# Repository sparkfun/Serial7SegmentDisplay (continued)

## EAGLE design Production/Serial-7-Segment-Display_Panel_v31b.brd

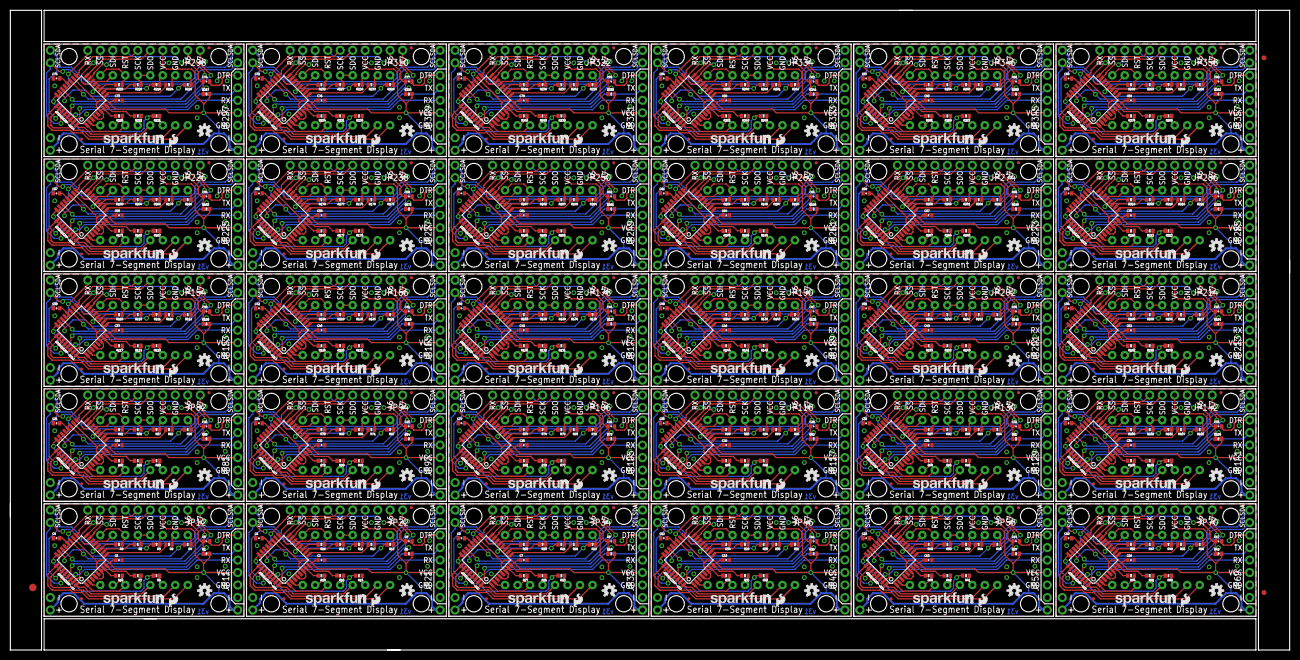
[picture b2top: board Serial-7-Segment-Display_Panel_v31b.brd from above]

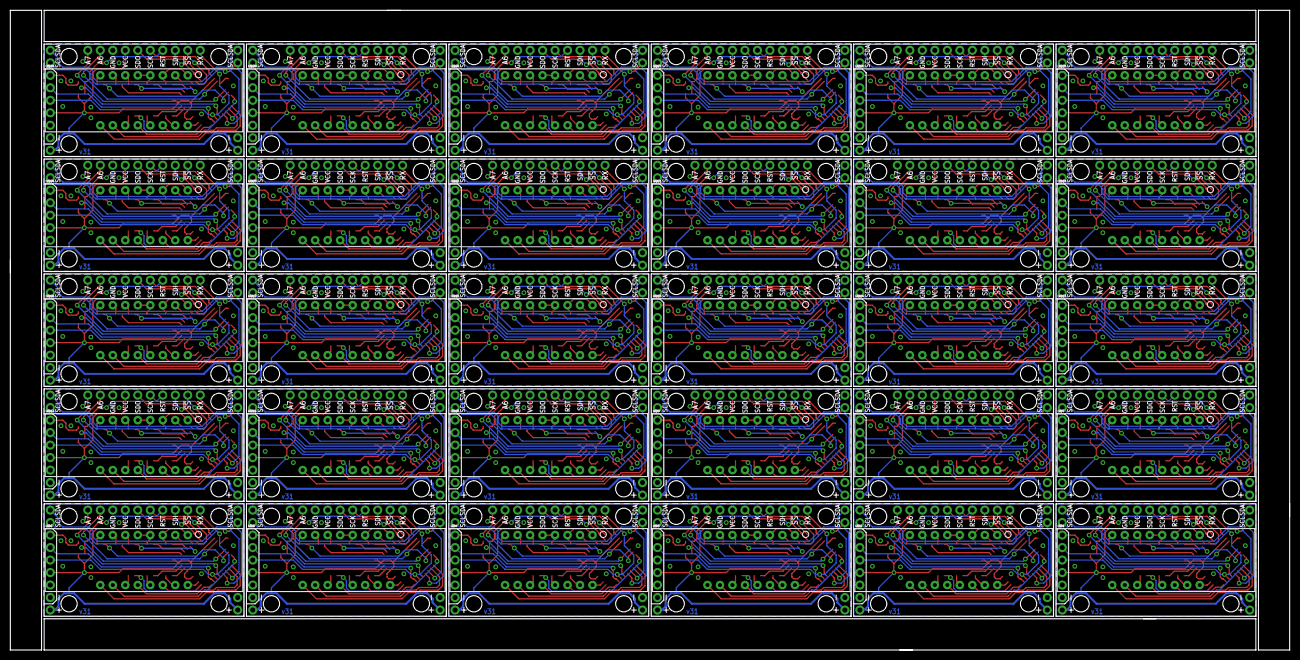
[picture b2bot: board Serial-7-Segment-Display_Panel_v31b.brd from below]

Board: 2 copper layers, 260.1 x 130.0 mm, 873 parts (30 on the bottom side), 1110 nets.

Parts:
ATMEGA328P-AU, ATMEGA328P-AU1, ATMEGA328P-AU2, ATMEGA328P-AU3, ATMEGA328P-AU4, ATMEGA328P-AU5, ATMEGA328P-AU6, ATMEGA328P-AU7, ATMEGA328P-AU8, ATMEGA328P-AU9, ATMEGA328P-AU10, ATMEGA328P-AU11, ATMEGA328P-AU12, ATMEGA328P-AU13, ATMEGA328P-AU14, ATMEGA328P-AU15, ATMEGA328P-AU16, ATMEGA328P-AU17, ATMEGA328P-AU18, ATMEGA328P-AU19, ATMEGA328P-AU20, ATMEGA328P-AU21, ATMEGA328P-AU22, ATMEGA328P-AU23, ATMEGA328P-AU24, ATMEGA328P-AU25, ATMEGA328P-AU26, ATMEGA328P-AU27, ATMEGA328P-AU28, ATMEGA328P-AU29: ATMEGA328P-AU; TQFP32-08
C1, C2, C3, C4, C5, C6, C7, C8, C9, C10, C11, C12, C13, C14, C15, C16, C17, C18, C19, C20, C21, C22, C23, C24, C25, C26, C27, C28, C29, C30, C31, C32, C33, C34, C35, C36, C37, C38, C39, C40, C41, C42, C43, C44, C45, C46, C47, C48, C49, C50, C51, C52, C53, C54, C55, C56, C57, C58, C59, C60, C61, C62, C63, C64, C65, C66, C67, C68, C69, C70, C71, C72, C73, C74, C75, C76, C77, C78, C79, C80, C81, C82, C83, C84, C85, C86, C87, C88, C89, C90: 0.1uF; 0402-CAP
E$1: FIDUCIAL-1.5X3
E$5, E$6: FIDUCIAL-1X2
JP1, JP3, JP4, JP5, JP13, JP14, JP15, JP16, JP25, JP26, JP27, JP28, JP37, JP38, JP39, JP40, JP49, JP50, JP51, JP52, JP61, JP62, JP63, JP64, JP73, JP74, JP75, JP76, JP85, JP86, JP87, JP88, JP97, JP98, JP99, JP100, JP109, JP110, JP111, JP112, JP121, JP122, JP123, JP124, JP133, JP134, JP135, JP136, JP145, JP146, JP147, JP148, JP157, JP158, JP159, JP160, JP169, JP170, JP171, JP172, JP181, JP182, JP183, JP184, JP193, JP194, JP195, JP196, JP205, JP206, JP207, JP208, JP217, JP218, JP219, JP220, JP229, JP230, JP231, JP232, JP241, JP242, JP243, JP244, JP253, JP254, JP255, JP256, JP265, JP266, JP267, JP268, JP277, JP278, JP279, JP280, JP289, JP290, JP291, JP292, JP301, JP302, JP303, JP304, JP313, JP314, JP315, JP316, JP325, JP326, JP327, JP328, JP337, JP338, JP339, JP340, JP349, JP350, JP351, JP352: STAND-OFF
JP2, JP6, JP7, JP8, JP17, JP18, JP19, JP20, JP29, JP30, JP31, JP32, JP41, JP42, JP43, JP44, JP53, JP54, JP55, JP56, JP65, JP66, JP67, JP68, JP77, JP78, JP79, JP80, JP89, JP90, JP91, JP92, JP101, JP102, JP103, JP104, JP113, JP114, JP115, JP116, JP125, JP126, JP127, JP128, JP137, JP138, JP139, JP140, JP149, JP150, JP151, JP152, JP161, JP162, JP163, JP164, JP173, JP174, JP175, JP176, JP185, JP186, JP187, JP188, JP197, JP198, JP199, JP200, JP209, JP210, JP211, JP212, JP221, JP222, JP223, JP224, JP233, JP234, JP235, JP236, JP245, JP246, JP247, JP248, JP257, JP258, JP259, JP260, JP269, JP270, JP271, JP272, JP281, JP282, JP283, JP284, JP293, JP294, JP295, JP296, JP305, JP306, JP307, JP308, JP317, JP318, JP319, JP320, JP329, JP330, JP331, JP332, JP341, JP342, JP343, JP344, JP353, JP354, JP355, JP356: 1X02_NO_SILK
JP9, JP10, JP23, JP24, JP35, JP36, JP47, JP48, JP59, JP60, JP71, JP72, JP83, JP84, JP95, JP96, JP107, JP108, JP119, JP120, JP131, JP132, JP143, JP144, JP155, JP156, JP167, JP168, JP179, JP180, JP191, JP192, JP203, JP204, JP215, JP216, JP227, JP228, JP239, JP240, JP251, JP252, JP263, JP264, JP275, JP276, JP287, JP288, JP299, JP300, JP311, JP312, JP323, JP324, JP335, JP336, JP347, JP348, JP359, JP360: FIDUCIALUFIDUCIAL; MICRO-FIDUCIAL
JP11, JP21, JP33, JP45, JP57, JP69, JP81, JP93, JP105, JP117, JP129, JP141, JP153, JP165, JP177, JP189, JP201, JP213, JP225, JP237, JP249, JP261, JP273, JP285, JP297, JP309, JP321, JP333, JP345, JP357: 1X05_NO_SILK
JP12, JP22, JP34, JP46, JP58, JP70, JP82, JP94, JP106, JP118, JP130, JP142, JP154, JP166, JP178, JP190, JP202, JP214, JP226, JP238, JP250, JP262, JP274, JP286, JP298, JP310, JP322, JP334, JP346, JP358: M10SIP_NS; 1X10_NO_SILK
LED1, LED2, LED3, LED4, LED5, LED6, LED7, LED8, LED9, LED10, LED11, LED12, LED13, LED14, LED15, LED16, LED17, LED18, LED19, LED20, LED21, LED22, LED23, LED24, LED25, LED26, LED27, LED28, LED29, LED30: 7-SEGMENT-4DIGIT-YOUNGSUN
R1, R5, R19, R28, R37, R46, R55, R64, R73, R82, R91, R100, R109, R118, R127, R136, R145, R154, R163, R172, R181, R190, R199, R208, R217, R226, R235, R244, R253, R262: 10k; 0402-RES
R2, R3, R4, R6, R7, R8, R9, R10, R11, R12, R13, R14, R15, R16, R17, R18, R20, R21, R22, R23, R24, R25, R26, R27, R29, R30, R31, R32, R33, R34, R35, R36, R38, R39, R40, R41, R42, R43, R44, R45, R47, R48, R49, R50, R51, R52, R53, R54, R56, R57, R58, R59, R60, R61, R62, R63, R65, R66, R67, R68, R69, R70, R71, R72, R74, R75, R76, R77, R78, R79, R80, R81, R83, R84, R85, R86, R87, R88, R89, R90, R92, R93, R94, R95, R96, R97, R98, R99, R101, R102, R103, R104, R105, R106, R107, R108, R110, R111, R112, R113, R114, R115, R116, R117, R119, R120, R121, R122, R123, R124, R125, R126, R128, R129, R130, R131, R132, R133, R134, R135, R137, R138, R139, R140, R141, R142, R143, R144, R146, R147, R148, R149, R150, R151, R152, R153, R155, R156, R157, R158, R159, R160, R161, R162, R164, R165, R166, R167, R168, R169, R170, R171, R173, R174, R175, R176, R177, R178, R179, R180, R182, R183, R184, R185, R186, R187, R188, R189, R191, R192, R193, R194, R195, R196, R197, R198, R200, R201, R202, R203, R204, R205, R206, R207, R209, R210, R211, R212, R213, R214, R215, R216, R218, R219, R220, R221, R222, R223, R224, R225, R227, R228, R229, R230, R231, R232, R233, R234, R236, R237, R238, R239, R240, R241, R242, R243, R245, R246, R247, R248, R249, R250, R251, R252, R254, R255, R256, R257, R258, R259, R260, R261, R263, R264, R265, R266, R267, R268, R269, R270: 1k; 0402-RES
U$1, U$3, U$7, U$10, U$13, U$16, U$19, U$22, U$25, U$28, U$31, U$34, U$37, U$40, U$43, U$46, U$49, U$52, U$55, U$58, U$61, U$64, U$67, U$70, U$73, U$76, U$79, U$82, U$85, U$88: LOGO-SFENW2; SFE-NEW-WEB
U$2, U$5, U$8, U$11, U$14, U$17, U$20, U$23, U$26, U$29, U$32, U$35, U$38, U$41, U$44, U$47, U$50, U$53, U$56, U$59, U$62, U$65, U$68, U$71, U$74, U$77, U$80, U$83, U$86, U$89: LOGO-SFESK; SFE-LOGO-FLAME
U$4, U$6, U$9, U$12, U$15, U$18, U$21, U$24, U$27, U$30, U$33, U$36, U$39, U$42, U$45, U$48, U$51, U$54, U$57, U$60, U$63, U$66, U$69, U$72, U$75, U$78, U$81, U$84, U$87, U$90: OSHW-LOGOS; OSHW-LOGO-S

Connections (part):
!SS: ATMEGA328P-AU.14, JP12.9
!SS1: ATMEGA328P-AU1.14, JP22.9
!SS2: ATMEGA328P-AU2.14, JP34.9
!SS3: ATMEGA328P-AU3.14, JP46.9
!SS4: ATMEGA328P-AU4.14, JP58.9
!SS5: ATMEGA328P-AU5.14, JP70.9
!SS6: ATMEGA328P-AU6.14, JP82.9
!SS7: ATMEGA328P-AU7.14, JP94.9
!SS8: ATMEGA328P-AU8.14, JP106.9
!SS9: ATMEGA328P-AU9.14, JP118.9
!SS10: ATMEGA328P-AU10.14, JP130.9
!SS11: ATMEGA328P-AU11.14, JP142.9
!SS12: ATMEGA328P-AU12.14, JP154.9
!SS13: ATMEGA328P-AU13.14, JP166.9
!SS14: ATMEGA328P-AU14.14, JP178.9
!SS15: ATMEGA328P-AU15.14, JP190.9
!SS16: ATMEGA328P-AU16.14, JP202.9
!SS17: ATMEGA328P-AU17.14, JP214.9
!SS18: ATMEGA328P-AU18.14, JP226.9
!SS19: ATMEGA328P-AU19.14, JP238.9
!SS20: ATMEGA328P-AU20.14, JP250.9
!SS21: ATMEGA328P-AU21.14, JP262.9
!SS22: ATMEGA328P-AU22.14, JP274.9
!SS23: ATMEGA328P-AU23.14, JP286.9
!SS24: ATMEGA328P-AU24.14, JP298.9
!SS25: ATMEGA328P-AU25.14, JP310.9
!SS26: ATMEGA328P-AU26.14, JP322.9
!SS27: ATMEGA328P-AU27.14, JP334.9
!SS28: ATMEGA328P-AU28.14, JP346.9
!SS29: ATMEGA328P-AU29.14, JP358.9
A/COL: ATMEGA328P-AU.10, R2.2
A/COL1: ATMEGA328P-AU1.10, R11.2
A/COL2: ATMEGA328P-AU2.10, R20.2
A/COL3: ATMEGA328P-AU3.10, R29.2
A/COL4: ATMEGA328P-AU4.10, R38.2
A/COL5: ATMEGA328P-AU5.10, R47.2
A/COL6: ATMEGA328P-AU6.10, R56.2
A/COL7: ATMEGA328P-AU7.10, R65.2
A/COL8: ATMEGA328P-AU8.10, R74.2
A/COL9: ATMEGA328P-AU9.10, R83.2
A/COL10: ATMEGA328P-AU10.10, R92.2
A/COL11: ATMEGA328P-AU11.10, R101.2
A/COL12: ATMEGA328P-AU12.10, R110.2
A/COL13: ATMEGA328P-AU13.10, R119.2
A/COL14: ATMEGA328P-AU14.10, R128.2
A/COL15: ATMEGA328P-AU15.10, R137.2
A/COL16: ATMEGA328P-AU16.10, R146.2
A/COL17: ATMEGA328P-AU17.10, R155.2
A/COL18: ATMEGA328P-AU18.10, R164.2
A/COL19: ATMEGA328P-AU19.10, R173.2
A/COL20: ATMEGA328P-AU20.10, R182.2
A/COL21: ATMEGA328P-AU21.10, R191.2
A/COL22: ATMEGA328P-AU22.10, R200.2
A/COL23: ATMEGA328P-AU23.10, R209.2
A/COL24: ATMEGA328P-AU24.10, R218.2
A/COL25: ATMEGA328P-AU25.10, R227.2
A/COL26: ATMEGA328P-AU26.10, R236.2
A/COL27: ATMEGA328P-AU27.10, R245.2
A/COL28: ATMEGA328P-AU28.10, R254.2
A/COL29: ATMEGA328P-AU29.10, R263.2
ADC1: ATMEGA328P-AU1.19, JP22.2
ADC2: ATMEGA328P-AU1.22, JP22.1
ADC3: ATMEGA328P-AU2.19, JP34.2
ADC4: ATMEGA328P-AU2.22, JP34.1
ADC5: ATMEGA328P-AU3.19, JP46.2
ADC6: ATMEGA328P-AU.19, JP12.2
ADC7: ATMEGA328P-AU.22, JP12.1
ADC8: ATMEGA328P-AU3.22, JP46.1
ADC9: ATMEGA328P-AU4.19, JP58.2
ADC10: ATMEGA328P-AU4.22, JP58.1
ADC11: ATMEGA328P-AU5.19, JP70.2
ADC12: ATMEGA328P-AU5.22, JP70.1
ADC13: ATMEGA328P-AU6.19, JP82.2
ADC14: ATMEGA328P-AU6.22, JP82.1
ADC15: ATMEGA328P-AU7.19, JP94.2
ADC16: ATMEGA328P-AU7.22, JP94.1
ADC17: ATMEGA328P-AU8.19, JP106.2
ADC18: ATMEGA328P-AU8.22, JP106.1
ADC19: ATMEGA328P-AU9.19, JP118.2
ADC20: ATMEGA328P-AU9.22, JP118.1
ADC21: ATMEGA328P-AU10.19, JP130.2
ADC22: ATMEGA328P-AU10.22, JP130.1
ADC23: ATMEGA328P-AU11.19, JP142.2
ADC24: ATMEGA328P-AU11.22, JP142.1
ADC25: ATMEGA328P-AU12.19, JP154.2
ADC26: ATMEGA328P-AU12.22, JP154.1
ADC27: ATMEGA328P-AU13.19, JP166.2
ADC28: ATMEGA328P-AU13.22, JP166.1
ADC29: ATMEGA328P-AU14.19, JP178.2
ADC30: ATMEGA328P-AU14.22, JP178.1
ADC31: ATMEGA328P-AU15.19, JP190.2
ADC32: ATMEGA328P-AU15.22, JP190.1
ADC33: ATMEGA328P-AU16.19, JP202.2
ADC34: ATMEGA328P-AU16.22, JP202.1
ADC35: ATMEGA328P-AU17.19, JP214.2
ADC36: ATMEGA328P-AU17.22, JP214.1
ADC37: ATMEGA328P-AU18.19, JP226.2
ADC38: ATMEGA328P-AU18.22, JP226.1
ADC39: ATMEGA328P-AU19.19, JP238.2
ADC40: ATMEGA328P-AU19.22, JP238.1
ADC41: ATMEGA328P-AU20.19, JP250.2
ADC42: ATMEGA328P-AU20.22, JP250.1
ADC43: ATMEGA328P-AU21.19, JP262.2
ADC44: ATMEGA328P-AU21.22, JP262.1
ADC45: ATMEGA328P-AU22.19, JP274.2
ADC46: ATMEGA328P-AU22.22, JP274.1
ADC47: ATMEGA328P-AU23.19, JP286.2
ADC48: ATMEGA328P-AU23.22, JP286.1
ADC49: ATMEGA328P-AU24.19, JP298.2
ADC50: ATMEGA328P-AU24.22, JP298.1
ADC51: ATMEGA328P-AU25.19, JP310.2
ADC52: ATMEGA328P-AU25.22, JP310.1
ADC53: ATMEGA328P-AU26.19, JP322.2
ADC54: ATMEGA328P-AU26.22, JP322.1
ADC55: ATMEGA328P-AU27.19, JP334.2
ADC56: ATMEGA328P-AU27.22, JP334.1
ADC57: ATMEGA328P-AU28.19, JP346.2
ADC58: ATMEGA328P-AU28.22, JP346.1
ADC59: ATMEGA328P-AU29.19, JP358.2
ADC60: ATMEGA328P-AU29.22, JP358.1
APOSA: ATMEGA328P-AU.13, LED1.10
APOSA1: ATMEGA328P-AU1.13, LED2.10
APOSA2: ATMEGA328P-AU2.13, LED3.10
APOSA3: ATMEGA328P-AU3.13, LED4.10
APOSA4: ATMEGA328P-AU4.13, LED5.10
APOSA5: ATMEGA328P-AU5.13, LED6.10
APOSA6: ATMEGA328P-AU6.13, LED7.10
APOSA7: ATMEGA328P-AU7.13, LED8.10
APOSA8: ATMEGA328P-AU8.13, LED9.10
APOSA9: ATMEGA328P-AU9.13, LED10.10
APOSA10: ATMEGA328P-AU10.13, LED11.10
APOSA11: ATMEGA328P-AU11.13, LED12.10
APOSA12: ATMEGA328P-AU12.13, LED13.10
APOSA13: ATMEGA328P-AU13.13, LED14.10
APOSA14: ATMEGA328P-AU14.13, LED15.10
APOSA15: ATMEGA328P-AU15.13, LED16.10
APOSA16: ATMEGA328P-AU16.13, LED17.10
APOSA17: ATMEGA328P-AU17.13, LED18.10
APOSA18: ATMEGA328P-AU18.13, LED19.10
APOSA19: ATMEGA328P-AU19.13, LED20.10
APOSA20: ATMEGA328P-AU20.13, LED21.10
APOSA21: ATMEGA328P-AU21.13, LED22.10
APOSA22: ATMEGA328P-AU22.13, LED23.10
APOSA23: ATMEGA328P-AU23.13, LED24.10
APOSA24: ATMEGA328P-AU24.13, LED25.10
APOSA25: ATMEGA328P-AU25.13, LED26.10
APOSA26: ATMEGA328P-AU26.13, LED27.10
APOSA27: ATMEGA328P-AU27.13, LED28.10
APOSA28: ATMEGA328P-AU28.13, LED29.10
APOSA29: ATMEGA328P-AU29.13, LED30.10
B: ATMEGA328P-AU.12, R3.2
B1: ATMEGA328P-AU1.12, R12.2
B2: ATMEGA328P-AU2.12, R21.2
B3: ATMEGA328P-AU3.12, R30.2
B4: ATMEGA328P-AU4.12, R39.2
B5: ATMEGA328P-AU5.12, R48.2
B6: ATMEGA328P-AU6.12, R57.2
B7: ATMEGA328P-AU7.12, R66.2
B8: ATMEGA328P-AU8.12, R75.2
B9: ATMEGA328P-AU9.12, R84.2
B10: ATMEGA328P-AU10.12, R93.2
B11: ATMEGA328P-AU11.12, R102.2
B12: ATMEGA328P-AU12.12, R111.2
B13: ATMEGA328P-AU13.12, R120.2
B14: ATMEGA328P-AU14.12, R129.2
B15: ATMEGA328P-AU15.12, R138.2
B16: ATMEGA328P-AU16.12, R147.2
B17: ATMEGA328P-AU17.12, R156.2
B18: ATMEGA328P-AU18.12, R165.2
B19: ATMEGA328P-AU19.12, R174.2
B20: ATMEGA328P-AU20.12, R183.2
B21: ATMEGA328P-AU21.12, R192.2
B22: ATMEGA328P-AU22.12, R201.2
B23: ATMEGA328P-AU23.12, R210.2
B24: ATMEGA328P-AU24.12, R219.2
B25: ATMEGA328P-AU25.12, R228.2
B26: ATMEGA328P-AU26.12, R237.2
B27: ATMEGA328P-AU27.12, R246.2
B28: ATMEGA328P-AU28.12, R255.2
B29: ATMEGA328P-AU29.12, R264.2
C: ATMEGA328P-AU.23, R4.2
C1: ATMEGA328P-AU1.23, R13.2
C2: ATMEGA328P-AU2.23, R22.2
C3: ATMEGA328P-AU3.23, R31.2
C4: ATMEGA328P-AU4.23, R40.2
C5: ATMEGA328P-AU5.23, R49.2
C6: ATMEGA328P-AU6.23, R58.2
C7: ATMEGA328P-AU7.23, R67.2
C8: ATMEGA328P-AU8.23, R76.2
C9: ATMEGA328P-AU9.23, R85.2
C10: ATMEGA328P-AU10.23, R94.2
C11: ATMEGA328P-AU11.23, R103.2
C12: ATMEGA328P-AU12.23, R112.2
C13: ATMEGA328P-AU13.23, R121.2
C14: ATMEGA328P-AU14.23, R130.2
C15: ATMEGA328P-AU15.23, R139.2
C16: ATMEGA328P-AU16.23, R148.2
C17: ATMEGA328P-AU17.23, R157.2
C18: ATMEGA328P-AU18.23, R166.2
C19: ATMEGA328P-AU19.23, R175.2
C20: ATMEGA328P-AU20.23, R184.2
C21: ATMEGA328P-AU21.23, R193.2
C22: ATMEGA328P-AU22.23, R202.2
C23: ATMEGA328P-AU23.23, R211.2
C24: ATMEGA328P-AU24.23, R220.2
C25: ATMEGA328P-AU25.23, R229.2
C26: ATMEGA328P-AU26.23, R238.2
C27: ATMEGA328P-AU27.23, R247.2
C28: ATMEGA328P-AU28.23, R256.2
C29: ATMEGA328P-AU29.23, R265.2
COLA: ATMEGA328P-AU.32, LED1.4
COLA1: ATMEGA328P-AU1.32, LED2.4
COLA2: ATMEGA328P-AU2.32, LED3.4
COLA3: ATMEGA328P-AU3.32, LED4.4
COLA4: ATMEGA328P-AU4.32, LED5.4
COLA5: ATMEGA328P-AU5.32, LED6.4
COLA6: ATMEGA328P-AU6.32, LED7.4
COLA7: ATMEGA328P-AU7.32, LED8.4
COLA8: ATMEGA328P-AU8.32, LED9.4
COLA9: ATMEGA328P-AU9.32, LED10.4
COLA10: ATMEGA328P-AU10.32, LED11.4
COLA11: ATMEGA328P-AU11.32, LED12.4
COLA12: ATMEGA328P-AU12.32, LED13.4
COLA13: ATMEGA328P-AU13.32, LED14.4
COLA14: ATMEGA328P-AU14.32, LED15.4
COLA15: ATMEGA328P-AU15.32, LED16.4
COLA16: ATMEGA328P-AU16.32, LED17.4
COLA17: ATMEGA328P-AU17.32, LED18.4
COLA18: ATMEGA328P-AU18.32, LED19.4
COLA19: ATMEGA328P-AU19.32, LED20.4
COLA20: ATMEGA328P-AU20.32, LED21.4
COLA21: ATMEGA328P-AU21.32, LED22.4
COLA22: ATMEGA328P-AU22.32, LED23.4
COLA23: ATMEGA328P-AU23.32, LED24.4
COLA24: ATMEGA328P-AU24.32, LED25.4
COLA25: ATMEGA328P-AU25.32, LED26.4
COLA26: ATMEGA328P-AU26.32, LED27.4
COLA27: ATMEGA328P-AU27.32, LED28.4
COLA28: ATMEGA328P-AU28.32, LED29.4
COLA29: ATMEGA328P-AU29.32, LED30.4
D: ATMEGA328P-AU.24, R6.2
D1: ATMEGA328P-AU1.24, R14.2
D2: ATMEGA328P-AU2.24, R23.2
D3: ATMEGA328P-AU3.24, R32.2
D4: ATMEGA328P-AU4.24, R41.2
D5: ATMEGA328P-AU5.24, R50.2
D6: ATMEGA328P-AU6.24, R59.2
D7: ATMEGA328P-AU7.24, R68.2
D8: ATMEGA328P-AU8.24, R77.2
D9: ATMEGA328P-AU9.24, R86.2
D10: ATMEGA328P-AU10.24, R95.2
D11: ATMEGA328P-AU11.24, R104.2
D12: ATMEGA328P-AU12.24, R113.2
D13: ATMEGA328P-AU13.24, R122.2
D14: ATMEGA328P-AU14.24, R131.2
D15: ATMEGA328P-AU15.24, R140.2
D16: ATMEGA328P-AU16.24, R149.2
D17: ATMEGA328P-AU17.24, R158.2
D18: ATMEGA328P-AU18.24, R167.2
D19: ATMEGA328P-AU19.24, R176.2
D20: ATMEGA328P-AU20.24, R185.2
D21: ATMEGA328P-AU21.24, R194.2
D22: ATMEGA328P-AU22.24, R203.2
D23: ATMEGA328P-AU23.24, R212.2
D24: ATMEGA328P-AU24.24, R221.2
D25: ATMEGA328P-AU25.24, R230.2
D26: ATMEGA328P-AU26.24, R239.2
D27: ATMEGA328P-AU27.24, R248.2
D28: ATMEGA328P-AU28.24, R257.2
D29: ATMEGA328P-AU29.24, R266.2
DIG1: ATMEGA328P-AU.25, LED1.1
DIG2: ATMEGA328P-AU.26, LED1.2
DIG3: ATMEGA328P-AU.1, LED1.6
DIG4: ATMEGA328P-AU.2, LED1.8
DIG5: ATMEGA328P-AU1.2, LED2.8
DIG6: ATMEGA328P-AU1.1, LED2.6
DIG7: ATMEGA328P-AU1.26, LED2.2
DIG8: ATMEGA328P-AU1.25, LED2.1
DIG9: ATMEGA328P-AU2.2, LED3.8
DIG10: ATMEGA328P-AU2.1, LED3.6
DIG11: ATMEGA328P-AU2.26, LED3.2
DIG12: ATMEGA328P-AU2.25, LED3.1
DIG13: ATMEGA328P-AU3.2, LED4.8
DIG14: ATMEGA328P-AU3.1, LED4.6
DIG15: ATMEGA328P-AU3.26, LED4.2
DIG16: ATMEGA328P-AU3.25, LED4.1
DIG17: ATMEGA328P-AU4.2, LED5.8
DIG18: ATMEGA328P-AU4.1, LED5.6
DIG19: ATMEGA328P-AU4.26, LED5.2
DIG20: ATMEGA328P-AU4.25, LED5.1
DIG21: ATMEGA328P-AU5.2, LED6.8
DIG22: ATMEGA328P-AU5.1, LED6.6
DIG23: ATMEGA328P-AU5.26, LED6.2
DIG24: ATMEGA328P-AU5.25, LED6.1
DIG25: ATMEGA328P-AU6.2, LED7.8
DIG26: ATMEGA328P-AU6.1, LED7.6
DIG27: ATMEGA328P-AU6.26, LED7.2
DIG28: ATMEGA328P-AU6.25, LED7.1
DIG29: ATMEGA328P-AU7.2, LED8.8
DIG30: ATMEGA328P-AU7.1, LED8.6
DIG31: ATMEGA328P-AU7.26, LED8.2
DIG32: ATMEGA328P-AU7.25, LED8.1
DIG33: ATMEGA328P-AU8.2, LED9.8
DIG34: ATMEGA328P-AU8.1, LED9.6
DIG35: ATMEGA328P-AU8.26, LED9.2
DIG36: ATMEGA328P-AU8.25, LED9.1
DIG37: ATMEGA328P-AU9.2, LED10.8
DIG38: ATMEGA328P-AU9.1, LED10.6
DIG39: ATMEGA328P-AU9.26, LED10.2
DIG40: ATMEGA328P-AU9.25, LED10.1
DIG41: ATMEGA328P-AU10.2, LED11.8
DIG42: ATMEGA328P-AU10.1, LED11.6
DIG43: ATMEGA328P-AU10.26, LED11.2
DIG44: ATMEGA328P-AU10.25, LED11.1
DIG45: ATMEGA328P-AU11.2, LED12.8
DIG46: ATMEGA328P-AU11.1, LED12.6
DIG47: ATMEGA328P-AU11.26, LED12.2
DIG48: ATMEGA328P-AU11.25, LED12.1
DIG49: ATMEGA328P-AU12.2, LED13.8
DIG50: ATMEGA328P-AU12.1, LED13.6
DIG51: ATMEGA328P-AU12.26, LED13.2
DIG52: ATMEGA328P-AU12.25, LED13.1
DIG53: ATMEGA328P-AU13.2, LED14.8
DIG54: ATMEGA328P-AU13.1, LED14.6
DIG55: ATMEGA328P-AU13.26, LED14.2
DIG56: ATMEGA328P-AU13.25, LED14.1
DIG57: ATMEGA328P-AU14.2, LED15.8
DIG58: ATMEGA328P-AU14.1, LED15.6
DIG59: ATMEGA328P-AU14.26, LED15.2
DIG60: ATMEGA328P-AU14.25, LED15.1
DIG61: ATMEGA328P-AU15.2, LED16.8
DIG62: ATMEGA328P-AU15.1, LED16.6
DIG63: ATMEGA328P-AU15.26, LED16.2
DIG64: ATMEGA328P-AU15.25, LED16.1
DIG65: ATMEGA328P-AU16.2, LED17.8
DIG66: ATMEGA328P-AU16.1, LED17.6
DIG67: ATMEGA328P-AU16.26, LED17.2
DIG68: ATMEGA328P-AU16.25, LED17.1
DIG69: ATMEGA328P-AU17.2, LED18.8
DIG70: ATMEGA328P-AU17.1, LED18.6
DIG71: ATMEGA328P-AU17.26, LED18.2
DIG72: ATMEGA328P-AU17.25, LED18.1
DIG73: ATMEGA328P-AU18.2, LED19.8
DIG74: ATMEGA328P-AU18.1, LED19.6
DIG75: ATMEGA328P-AU18.26, LED19.2
DIG76: ATMEGA328P-AU18.25, LED19.1
DIG77: ATMEGA328P-AU19.2, LED20.8
DIG78: ATMEGA328P-AU19.1, LED20.6
DIG79: ATMEGA328P-AU19.26, LED20.2
DIG80: ATMEGA328P-AU19.25, LED20.1
DIG81: ATMEGA328P-AU20.2, LED21.8
DIG82: ATMEGA328P-AU20.1, LED21.6
DIG83: ATMEGA328P-AU20.26, LED21.2
DIG84: ATMEGA328P-AU20.25, LED21.1
DIG85: ATMEGA328P-AU21.2, LED22.8
DIG86: ATMEGA328P-AU21.1, LED22.6
DIG87: ATMEGA328P-AU21.26, LED22.2
DIG88: ATMEGA328P-AU21.25, LED22.1
DIG89: ATMEGA328P-AU22.2, LED23.8
DIG90: ATMEGA328P-AU22.1, LED23.6
DIG91: ATMEGA328P-AU22.26, LED23.2
DIG92: ATMEGA328P-AU22.25, LED23.1
DIG93: ATMEGA328P-AU23.2, LED24.8
DIG94: ATMEGA328P-AU23.1, LED24.6
DIG95: ATMEGA328P-AU23.26, LED24.2
DIG96: ATMEGA328P-AU23.25, LED24.1
DIG97: ATMEGA328P-AU24.2, LED25.8
DIG98: ATMEGA328P-AU24.1, LED25.6
DIG99: ATMEGA328P-AU24.26, LED25.2
DIG100: ATMEGA328P-AU24.25, LED25.1
DIG101: ATMEGA328P-AU25.2, LED26.8
DIG102: ATMEGA328P-AU25.1, LED26.6
DIG103: ATMEGA328P-AU25.26, LED26.2
DIG104: ATMEGA328P-AU25.25, LED26.1
DIG105: ATMEGA328P-AU26.2, LED27.8
DIG106: ATMEGA328P-AU26.1, LED27.6
DIG107: ATMEGA328P-AU26.26, LED27.2
DIG108: ATMEGA328P-AU26.25, LED27.1
DIG109: ATMEGA328P-AU27.2, LED28.8
DIG110: ATMEGA328P-AU27.1, LED28.6
DIG111: ATMEGA328P-AU27.26, LED28.2
DIG112: ATMEGA328P-AU27.25, LED28.1
DIG113: ATMEGA328P-AU28.2, LED29.8
DIG114: ATMEGA328P-AU28.1, LED29.6
DIG115: ATMEGA328P-AU28.26, LED29.2
DIG116: ATMEGA328P-AU28.25, LED29.1
DIG117: ATMEGA328P-AU29.2, LED30.8
DIG118: ATMEGA328P-AU29.1, LED30.6
DIG119: ATMEGA328P-AU29.26, LED30.2
DIG120: ATMEGA328P-AU29.25, LED30.1
DP: ATMEGA328P-AU.7, R10.2
DP1: ATMEGA328P-AU1.7, R18.2
DP2: ATMEGA328P-AU2.7, R27.2
DP3: ATMEGA328P-AU3.7, R36.2
DP4: ATMEGA328P-AU4.7, R45.2
DP5: ATMEGA328P-AU5.7, R54.2
DP6: ATMEGA328P-AU6.7, R63.2
DP7: ATMEGA328P-AU7.7, R72.2
DP8: ATMEGA328P-AU8.7, R81.2
DP9: ATMEGA328P-AU9.7, R90.2
DP10: ATMEGA328P-AU10.7, R99.2
DP11: ATMEGA328P-AU11.7, R108.2
DP12: ATMEGA328P-AU12.7, R117.2
DP13: ATMEGA328P-AU13.7, R126.2
DP14: ATMEGA328P-AU14.7, R135.2
DP15: ATMEGA328P-AU15.7, R144.2
DP16: ATMEGA328P-AU16.7, R153.2
DP17: ATMEGA328P-AU17.7, R162.2
DP18: ATMEGA328P-AU18.7, R171.2
DP19: ATMEGA328P-AU19.7, R180.2
DP20: ATMEGA328P-AU20.7, R189.2
DP21: ATMEGA328P-AU21.7, R198.2
DP22: ATMEGA328P-AU22.7, R207.2
DP23: ATMEGA328P-AU23.7, R216.2
DP24: ATMEGA328P-AU24.7, R225.2
DP25: ATMEGA328P-AU25.7, R234.2
DP26: ATMEGA328P-AU26.7, R243.2
DP27: ATMEGA328P-AU27.7, R252.2
DP28: ATMEGA328P-AU28.7, R261.2
DP29: ATMEGA328P-AU29.7, R270.2
E: ATMEGA328P-AU.8, R7.2
E1: ATMEGA328P-AU1.8, R15.2
E2: ATMEGA328P-AU2.8, R24.2
E3: ATMEGA328P-AU3.8, R33.2
E4: ATMEGA328P-AU4.8, R42.2
E5: ATMEGA328P-AU5.8, R51.2
E6: ATMEGA328P-AU6.8, R60.2
E7: ATMEGA328P-AU7.8, R69.2
E8: ATMEGA328P-AU8.8, R78.2
E9: ATMEGA328P-AU9.8, R87.2
E10: ATMEGA328P-AU10.8, R96.2
E11: ATMEGA328P-AU11.8, R105.2
E12: ATMEGA328P-AU12.8, R114.2
E13: ATMEGA328P-AU13.8, R123.2
E14: ATMEGA328P-AU14.8, R132.2
E15: ATMEGA328P-AU15.8, R141.2
E16: ATMEGA328P-AU16.8, R150.2
E17: ATMEGA328P-AU17.8, R159.2
E18: ATMEGA328P-AU18.8, R168.2
E19: ATMEGA328P-AU19.8, R177.2
E20: ATMEGA328P-AU20.8, R186.2
E21: ATMEGA328P-AU21.8, R195.2
E22: ATMEGA328P-AU22.8, R204.2
E23: ATMEGA328P-AU23.8, R213.2
E24: ATMEGA328P-AU24.8, R222.2
E25: ATMEGA328P-AU25.8, R231.2
E26: ATMEGA328P-AU26.8, R240.2
E27: ATMEGA328P-AU27.8, R249.2
E28: ATMEGA328P-AU28.8, R258.2
E29: ATMEGA328P-AU29.8, R267.2
F: ATMEGA328P-AU.11, R8.2
F1: ATMEGA328P-AU1.11, R16.2
F2: ATMEGA328P-AU2.11, R25.2
F3: ATMEGA328P-AU3.11, R34.2
F4: ATMEGA328P-AU4.11, R43.2
F5: ATMEGA328P-AU5.11, R52.2
F6: ATMEGA328P-AU6.11, R61.2
F7: ATMEGA328P-AU7.11, R70.2
F8: ATMEGA328P-AU8.11, R79.2
F9: ATMEGA328P-AU9.11, R88.2
F10: ATMEGA328P-AU10.11, R97.2
F11: ATMEGA328P-AU11.11, R106.2
F12: ATMEGA328P-AU12.11, R115.2
F13: ATMEGA328P-AU13.11, R124.2
F14: ATMEGA328P-AU14.11, R133.2
F15: ATMEGA328P-AU15.11, R142.2
F16: ATMEGA328P-AU16.11, R151.2
F17: ATMEGA328P-AU17.11, R160.2
F18: ATMEGA328P-AU18.11, R169.2
F19: ATMEGA328P-AU19.11, R178.2
F20: ATMEGA328P-AU20.11, R187.2
F21: ATMEGA328P-AU21.11, R196.2
F22: ATMEGA328P-AU22.11, R205.2
F23: ATMEGA328P-AU23.11, R214.2
F24: ATMEGA328P-AU24.11, R223.2
F25: ATMEGA328P-AU25.11, R232.2
F26: ATMEGA328P-AU26.11, R241.2
F27: ATMEGA328P-AU27.11, R250.2
F28: ATMEGA328P-AU28.11, R259.2
F29: ATMEGA328P-AU29.11, R268.2
G/APOS: ATMEGA328P-AU.9, R9.2
G/APOS1: ATMEGA328P-AU1.9, R17.2
G/APOS2: ATMEGA328P-AU2.9, R26.2
G/APOS3: ATMEGA328P-AU3.9, R35.2
G/APOS4: ATMEGA328P-AU4.9, R44.2
G/APOS5: ATMEGA328P-AU5.9, R53.2
G/APOS6: ATMEGA328P-AU6.9, R62.2
G/APOS7: ATMEGA328P-AU7.9, R71.2
G/APOS8: ATMEGA328P-AU8.9, R80.2
G/APOS9: ATMEGA328P-AU9.9, R89.2
G/APOS10: ATMEGA328P-AU10.9, R98.2
G/APOS11: ATMEGA328P-AU11.9, R107.2
G/APOS12: ATMEGA328P-AU12.9, R116.2
G/APOS13: ATMEGA328P-AU13.9, R125.2
G/APOS14: ATMEGA328P-AU14.9, R134.2
G/APOS15: ATMEGA328P-AU15.9, R143.2
G/APOS16: ATMEGA328P-AU16.9, R152.2
G/APOS17: ATMEGA328P-AU17.9, R161.2
G/APOS18: ATMEGA328P-AU18.9, R170.2
G/APOS19: ATMEGA328P-AU19.9, R179.2
G/APOS20: ATMEGA328P-AU20.9, R188.2
G/APOS21: ATMEGA328P-AU21.9, R197.2
G/APOS22: ATMEGA328P-AU22.9, R206.2
G/APOS23: ATMEGA328P-AU23.9, R215.2
G/APOS24: ATMEGA328P-AU24.9, R224.2
G/APOS25: ATMEGA328P-AU25.9, R233.2
G/APOS26: ATMEGA328P-AU26.9, R242.2
G/APOS27: ATMEGA328P-AU27.9, R251.2
G/APOS28: ATMEGA328P-AU28.9, R260.2
G/APOS29: ATMEGA328P-AU29.9, R269.2
GND: ATMEGA328P-AU.3, ATMEGA328P-AU.5, ATMEGA328P-AU.21, C1.2, C4.1, JP6.2, JP8.2, JP11.1, JP12.3
GND1: ATMEGA328P-AU1.3, ATMEGA328P-AU1.5, ATMEGA328P-AU1.21, C2.2, C6.1, JP17.2, JP19.2, JP21.1, JP22.3
GND2: ATMEGA328P-AU2.3, ATMEGA328P-AU2.5, ATMEGA328P-AU2.21, C7.2, C9.1, JP29.2, JP31.2, JP33.1, JP34.3
GND3: ATMEGA328P-AU3.3, ATMEGA328P-AU3.5, ATMEGA328P-AU3.21, C10.2, C12.1, JP41.2, JP43.2, JP45.1, JP46.3
GND4: ATMEGA328P-AU4.3, ATMEGA328P-AU4.5, ATMEGA328P-AU4.21, C13.2, C15.1, JP53.2, JP55.2, JP57.1, JP58.3
GND5: ATMEGA328P-AU5.3, ATMEGA328P-AU5.5, ATMEGA328P-AU5.21, C16.2, C18.1, JP65.2, JP67.2, JP69.1, JP70.3
GND6: ATMEGA328P-AU6.3, ATMEGA328P-AU6.5, ATMEGA328P-AU6.21, C19.2, C21.1, JP77.2, JP79.2, JP81.1, JP82.3
GND7: ATMEGA328P-AU7.3, ATMEGA328P-AU7.5, ATMEGA328P-AU7.21, C22.2, C24.1, JP89.2, JP91.2, JP93.1, JP94.3
GND8: ATMEGA328P-AU8.3, ATMEGA328P-AU8.5, ATMEGA328P-AU8.21, C25.2, C27.1, JP101.2, JP103.2, JP105.1, JP106.3
GND9: ATMEGA328P-AU9.3, ATMEGA328P-AU9.5, ATMEGA328P-AU9.21, C28.2, C30.1, JP113.2, JP115.2, JP117.1, JP118.3
GND10: ATMEGA328P-AU10.3, ATMEGA328P-AU10.5, ATMEGA328P-AU10.21, C31.2, C33.1, JP125.2, JP127.2, JP129.1, JP130.3
GND11: ATMEGA328P-AU11.3, ATMEGA328P-AU11.5, ATMEGA328P-AU11.21, C34.2, C36.1, JP137.2, JP139.2, JP141.1, JP142.3
GND12: ATMEGA328P-AU12.3, ATMEGA328P-AU12.5, ATMEGA328P-AU12.21, C37.2, C39.1, JP149.2, JP151.2, JP153.1, JP154.3
GND13: ATMEGA328P-AU13.3, ATMEGA328P-AU13.5, ATMEGA328P-AU13.21, C40.2, C42.1, JP161.2, JP163.2, JP165.1, JP166.3
GND14: ATMEGA328P-AU14.3, ATMEGA328P-AU14.5, ATMEGA328P-AU14.21, C43.2, C45.1, JP173.2, JP175.2, JP177.1, JP178.3
GND15: ATMEGA328P-AU15.3, ATMEGA328P-AU15.5, ATMEGA328P-AU15.21, C46.2, C48.1, JP185.2, JP187.2, JP189.1, JP190.3
GND16: ATMEGA328P-AU16.3, ATMEGA328P-AU16.5, ATMEGA328P-AU16.21, C49.2, C51.1, JP197.2, JP199.2, JP201.1, JP202.3
GND17: ATMEGA328P-AU17.3, ATMEGA328P-AU17.5, ATMEGA328P-AU17.21, C52.2, C54.1, JP209.2, JP211.2, JP213.1, JP214.3
GND18: ATMEGA328P-AU18.3, ATMEGA328P-AU18.5, ATMEGA328P-AU18.21, C55.2, C57.1, JP221.2, JP223.2, JP225.1, JP226.3
GND19: ATMEGA328P-AU19.3, ATMEGA328P-AU19.5, ATMEGA328P-AU19.21, C58.2, C60.1, JP233.2, JP235.2, JP237.1, JP238.3
GND20: ATMEGA328P-AU20.3, ATMEGA328P-AU20.5, ATMEGA328P-AU20.21, C61.2, C63.1, JP245.2, JP247.2, JP249.1, JP250.3
GND21: ATMEGA328P-AU21.3, ATMEGA328P-AU21.5, ATMEGA328P-AU21.21, C64.2, C66.1, JP257.2, JP259.2, JP261.1, JP262.3
GND22: ATMEGA328P-AU22.3, ATMEGA328P-AU22.5, ATMEGA328P-AU22.21, C67.2, C69.1, JP269.2, JP271.2, JP273.1, JP274.3
GND23: ATMEGA328P-AU23.3, ATMEGA328P-AU23.5, ATMEGA328P-AU23.21, C70.2, C72.1, JP281.2, JP283.2, JP285.1, JP286.3
GND24: ATMEGA328P-AU24.3, ATMEGA328P-AU24.5, ATMEGA328P-AU24.21, C73.2, C75.1, JP293.2, JP295.2, JP297.1, JP298.3
GND25: ATMEGA328P-AU25.3, ATMEGA328P-AU25.5, ATMEGA328P-AU25.21, C76.2, C78.1, JP305.2, JP307.2, JP309.1, JP310.3
GND26: ATMEGA328P-AU26.3, ATMEGA328P-AU26.5, ATMEGA328P-AU26.21, C79.2, C81.1, JP317.2, JP319.2, JP321.1, JP322.3
GND27: ATMEGA328P-AU27.3, ATMEGA328P-AU27.5, ATMEGA328P-AU27.21, C82.2, C84.1, JP329.2, JP331.2, JP333.1, JP334.3
GND28: ATMEGA328P-AU28.3, ATMEGA328P-AU28.5, ATMEGA328P-AU28.21, C85.2, C87.1, JP341.2, JP343.2, JP345.1, JP346.3
GND29: ATMEGA328P-AU29.3, ATMEGA328P-AU29.5, ATMEGA328P-AU29.21, C88.2, C90.1, JP353.2, JP355.2, JP357.1, JP358.3
MISO: ATMEGA328P-AU.16, JP12.5
MISO1: ATMEGA328P-AU1.16, JP22.5
MISO2: ATMEGA328P-AU2.16, JP34.5
MISO3: ATMEGA328P-AU3.16, JP46.5
MISO4: ATMEGA328P-AU4.16, JP58.5
MISO5: ATMEGA328P-AU5.16, JP70.5
MISO6: ATMEGA328P-AU6.16, JP82.5
MISO7: ATMEGA328P-AU7.16, JP94.5
MISO8: ATMEGA328P-AU8.16, JP106.5
MISO9: ATMEGA328P-AU9.16, JP118.5
MISO10: ATMEGA328P-AU10.16, JP130.5
MISO11: ATMEGA328P-AU11.16, JP142.5
MISO12: ATMEGA328P-AU12.16, JP154.5
MISO13: ATMEGA328P-AU13.16, JP166.5
MISO14: ATMEGA328P-AU14.16, JP178.5
MISO15: ATMEGA328P-AU15.16, JP190.5
MISO16: ATMEGA328P-AU16.16, JP202.5
MISO17: ATMEGA328P-AU17.16, JP214.5
MISO18: ATMEGA328P-AU18.16, JP226.5
MISO19: ATMEGA328P-AU19.16, JP238.5
MISO20: ATMEGA328P-AU20.16, JP250.5
MISO21: ATMEGA328P-AU21.16, JP262.5
MISO22: ATMEGA328P-AU22.16, JP274.5
MISO23: ATMEGA328P-AU23.16, JP286.5
MISO24: ATMEGA328P-AU24.16, JP298.5
MISO25: ATMEGA328P-AU25.16, JP310.5
MISO26: ATMEGA328P-AU26.16, JP322.5
MISO27: ATMEGA328P-AU27.16, JP334.5
MISO28: ATMEGA328P-AU28.16, JP346.5
MISO29: ATMEGA328P-AU29.16, JP358.5
MOSI: ATMEGA328P-AU.15, JP12.8
MOSI1: ATMEGA328P-AU1.15, JP22.8
MOSI2: ATMEGA328P-AU2.15, JP34.8
MOSI3: ATMEGA328P-AU3.15, JP46.8
MOSI4: ATMEGA328P-AU4.15, JP58.8
MOSI5: ATMEGA328P-AU5.15, JP70.8
MOSI6: ATMEGA328P-AU6.15, JP82.8
MOSI7: ATMEGA328P-AU7.15, JP94.8
MOSI8: ATMEGA328P-AU8.15, JP106.8
MOSI9: ATMEGA328P-AU9.15, JP118.8
MOSI10: ATMEGA328P-AU10.15, JP130.8
MOSI11: ATMEGA328P-AU11.15, JP142.8
MOSI12: ATMEGA328P-AU12.15, JP154.8
MOSI13: ATMEGA328P-AU13.15, JP166.8
MOSI14: ATMEGA328P-AU14.15, JP178.8
MOSI15: ATMEGA328P-AU15.15, JP190.8
MOSI16: ATMEGA328P-AU16.15, JP202.8
MOSI17: ATMEGA328P-AU17.15, JP214.8
MOSI18: ATMEGA328P-AU18.15, JP226.8
MOSI19: ATMEGA328P-AU19.15, JP238.8
MOSI20: ATMEGA328P-AU20.15, JP250.8
MOSI21: ATMEGA328P-AU21.15, JP262.8
MOSI22: ATMEGA328P-AU22.15, JP274.8
MOSI23: ATMEGA328P-AU23.15, JP286.8
MOSI24: ATMEGA328P-AU24.15, JP298.8
MOSI25: ATMEGA328P-AU25.15, JP310.8
MOSI26: ATMEGA328P-AU26.15, JP322.8
MOSI27: ATMEGA328P-AU27.15, JP334.8
MOSI28: ATMEGA328P-AU28.15, JP346.8
MOSI29: ATMEGA328P-AU29.15, JP358.8
unnamed: ATMEGA328P-AU.20, C4.2
unnamed: LED1.7, R10.1
unnamed: LED1.15, R9.1
unnamed: LED1.9, LED1.11, R8.1
unnamed: LED1.5, R7.1
unnamed: LED1.3, R6.1
unnamed: LED2.7, R18.1
unnamed: LED1.16, R4.1
unnamed: LED1.14, R3.1
unnamed: LED1.12, LED1.13, R2.1
unnamed: LED2.15, R17.1
unnamed: LED2.9, LED2.11, R16.1
unnamed: C3.2, JP11.5
unnamed: LED2.5, R15.1
unnamed: LED2.3, R14.1
unnamed: LED2.16, R13.1
unnamed: LED2.14, R12.1
unnamed: LED2.12, LED2.13, R11.1
unnamed: C5.2, JP21.5
unnamed: ATMEGA328P-AU1.20, C6.2
unnamed: LED3.7, R27.1
unnamed: LED3.15, R26.1
unnamed: LED3.9, LED3.11, R25.1
unnamed: LED3.5, R24.1
unnamed: LED3.3, R23.1
unnamed: LED3.16, R22.1
unnamed: LED3.14, R21.1
unnamed: LED3.12, LED3.13, R20.1
unnamed: C8.2, JP33.5
unnamed: ATMEGA328P-AU2.20, C9.2
unnamed: LED4.7, R36.1
unnamed: LED4.15, R35.1
unnamed: LED4.9, LED4.11, R34.1
unnamed: LED4.5, R33.1
unnamed: LED4.3, R32.1
unnamed: LED4.16, R31.1
unnamed: LED4.14, R30.1
unnamed: LED4.12, LED4.13, R29.1
unnamed: C11.2, JP45.5
unnamed: ATMEGA328P-AU3.20, C12.2
unnamed: LED5.7, R45.1
unnamed: LED5.15, R44.1
unnamed: LED5.9, LED5.11, R43.1
unnamed: LED5.5, R42.1
unnamed: LED5.3, R41.1
unnamed: LED5.16, R40.1
unnamed: LED5.14, R39.1
unnamed: LED5.12, LED5.13, R38.1
unnamed: C14.2, JP57.5
unnamed: ATMEGA328P-AU4.20, C15.2
unnamed: LED6.7, R54.1
unnamed: LED6.15, R53.1
unnamed: LED6.9, LED6.11, R52.1
unnamed: LED6.5, R51.1
unnamed: LED6.3, R50.1
unnamed: LED6.16, R49.1
unnamed: LED6.14, R48.1
unnamed: LED6.12, LED6.13, R47.1
unnamed: C17.2, JP69.5
unnamed: ATMEGA328P-AU5.20, C18.2
unnamed: LED7.7, R63.1
unnamed: LED7.15, R62.1
unnamed: LED7.9, LED7.11, R61.1
unnamed: LED7.5, R60.1
unnamed: LED7.3, R59.1
unnamed: LED7.16, R58.1
unnamed: LED7.14, R57.1
unnamed: LED7.12, LED7.13, R56.1
unnamed: C20.2, JP81.5
unnamed: ATMEGA328P-AU6.20, C21.2
unnamed: LED8.7, R72.1
unnamed: LED8.15, R71.1
unnamed: LED8.9, LED8.11, R70.1
unnamed: LED8.5, R69.1
unnamed: LED8.3, R68.1
unnamed: LED8.16, R67.1
unnamed: LED8.14, R66.1
unnamed: LED8.12, LED8.13, R65.1
unnamed: C23.2, JP93.5
unnamed: ATMEGA328P-AU7.20, C24.2
unnamed: LED9.7, R81.1
unnamed: LED9.15, R80.1
unnamed: LED9.9, LED9.11, R79.1
unnamed: LED9.5, R78.1
unnamed: LED9.3, R77.1
unnamed: LED9.16, R76.1
unnamed: LED9.14, R75.1
unnamed: LED9.12, LED9.13, R74.1
unnamed: C26.2, JP105.5
unnamed: ATMEGA328P-AU8.20, C27.2
unnamed: LED10.7, R90.1
unnamed: LED10.15, R89.1
unnamed: LED10.9, LED10.11, R88.1
unnamed: LED10.5, R87.1
unnamed: LED10.3, R86.1
unnamed: LED10.16, R85.1
unnamed: LED10.14, R84.1
unnamed: LED10.12, LED10.13, R83.1
unnamed: C29.2, JP117.5
unnamed: ATMEGA328P-AU9.20, C30.2
unnamed: LED11.7, R99.1
unnamed: LED11.15, R98.1
unnamed: LED11.9, LED11.11, R97.1
unnamed: LED11.5, R96.1
unnamed: LED11.3, R95.1
unnamed: LED11.16, R94.1
unnamed: LED11.14, R93.1
unnamed: LED11.12, LED11.13, R92.1
unnamed: C32.2, JP129.5
unnamed: ATMEGA328P-AU10.20, C33.2
unnamed: LED12.7, R108.1
unnamed: LED12.15, R107.1
unnamed: LED12.9, LED12.11, R106.1
unnamed: LED12.5, R105.1
unnamed: LED12.3, R104.1
unnamed: LED12.16, R103.1
unnamed: LED12.14, R102.1
unnamed: LED12.12, LED12.13, R101.1
unnamed: C35.2, JP141.5
unnamed: ATMEGA328P-AU11.20, C36.2
unnamed: LED13.7, R117.1
unnamed: LED13.15, R116.1
unnamed: LED13.9, LED13.11, R115.1
unnamed: LED13.5, R114.1
unnamed: LED13.3, R113.1
unnamed: LED13.16, R112.1
unnamed: LED13.14, R111.1
unnamed: LED13.12, LED13.13, R110.1
unnamed: C38.2, JP153.5
unnamed: ATMEGA328P-AU12.20, C39.2
unnamed: LED14.7, R126.1
unnamed: LED14.15, R125.1
unnamed: LED14.9, LED14.11, R124.1
unnamed: LED14.5, R123.1
unnamed: LED14.3, R122.1
unnamed: LED14.16, R121.1
unnamed: LED14.14, R120.1
unnamed: LED14.12, LED14.13, R119.1
unnamed: C41.2, JP165.5
unnamed: ATMEGA328P-AU13.20, C42.2
unnamed: LED15.7, R135.1
unnamed: LED15.15, R134.1
unnamed: LED15.9, LED15.11, R133.1
unnamed: LED15.5, R132.1
unnamed: LED15.3, R131.1
unnamed: LED15.16, R130.1
unnamed: LED15.14, R129.1
unnamed: LED15.12, LED15.13, R128.1
unnamed: C44.2, JP177.5
unnamed: ATMEGA328P-AU14.20, C45.2
unnamed: LED16.7, R144.1
unnamed: LED16.15, R143.1
unnamed: LED16.9, LED16.11, R142.1
unnamed: LED16.5, R141.1
unnamed: LED16.3, R140.1
unnamed: LED16.16, R139.1
unnamed: LED16.14, R138.1
unnamed: LED16.12, LED16.13, R137.1
unnamed: C47.2, JP189.5
unnamed: ATMEGA328P-AU15.20, C48.2
unnamed: LED17.7, R153.1
unnamed: LED17.15, R152.1
unnamed: LED17.9, LED17.11, R151.1
unnamed: LED17.5, R150.1
unnamed: LED17.3, R149.1
unnamed: LED17.16, R148.1
unnamed: LED17.14, R147.1
unnamed: LED17.12, LED17.13, R146.1
unnamed: C50.2, JP201.5
unnamed: ATMEGA328P-AU16.20, C51.2
unnamed: LED18.7, R162.1
unnamed: LED18.15, R161.1
unnamed: LED18.9, LED18.11, R160.1
unnamed: LED18.5, R159.1
unnamed: LED18.3, R158.1
unnamed: LED18.16, R157.1
unnamed: LED18.14, R156.1
unnamed: LED18.12, LED18.13, R155.1
unnamed: C53.2, JP213.5
unnamed: ATMEGA328P-AU17.20, C54.2
unnamed: LED19.7, R171.1
unnamed: LED19.15, R170.1
unnamed: LED19.9, LED19.11, R169.1
unnamed: LED19.5, R168.1
unnamed: LED19.3, R167.1
unnamed: LED19.16, R166.1
unnamed: LED19.14, R165.1
unnamed: LED19.12, LED19.13, R164.1
unnamed: C56.2, JP225.5
unnamed: ATMEGA328P-AU18.20, C57.2
unnamed: LED20.7, R180.1
unnamed: LED20.15, R179.1
unnamed: LED20.9, LED20.11, R178.1
unnamed: LED20.5, R177.1
unnamed: LED20.3, R176.1
unnamed: LED20.16, R175.1
unnamed: LED20.14, R174.1
unnamed: LED20.12, LED20.13, R173.1
unnamed: C59.2, JP237.5
unnamed: ATMEGA328P-AU19.20, C60.2
unnamed: LED21.7, R189.1
unnamed: LED21.15, R188.1
unnamed: LED21.9, LED21.11, R187.1
unnamed: LED21.5, R186.1
unnamed: LED21.3, R185.1
unnamed: LED21.16, R184.1
unnamed: LED21.14, R183.1
unnamed: LED21.12, LED21.13, R182.1
unnamed: C62.2, JP249.5
unnamed: ATMEGA328P-AU20.20, C63.2
unnamed: LED22.7, R198.1
unnamed: LED22.15, R197.1
unnamed: LED22.9, LED22.11, R196.1
unnamed: LED22.5, R195.1
unnamed: LED22.3, R194.1
unnamed: LED22.16, R193.1
unnamed: LED22.14, R192.1
unnamed: LED22.12, LED22.13, R191.1
unnamed: C65.2, JP261.5
unnamed: ATMEGA328P-AU21.20, C66.2
unnamed: LED23.7, R207.1
unnamed: LED23.15, R206.1
unnamed: LED23.9, LED23.11, R205.1
unnamed: LED23.5, R204.1
unnamed: LED23.3, R203.1
unnamed: LED23.16, R202.1
unnamed: LED23.14, R201.1
unnamed: LED23.12, LED23.13, R200.1
unnamed: C68.2, JP273.5
unnamed: ATMEGA328P-AU22.20, C69.2
unnamed: LED24.7, R216.1
unnamed: LED24.15, R215.1
unnamed: LED24.9, LED24.11, R214.1
unnamed: LED24.5, R213.1
unnamed: LED24.3, R212.1
unnamed: LED24.16, R211.1
unnamed: LED24.14, R210.1
unnamed: LED24.12, LED24.13, R209.1
unnamed: C71.2, JP285.5
unnamed: ATMEGA328P-AU23.20, C72.2
unnamed: LED25.7, R225.1
unnamed: LED25.15, R224.1
unnamed: LED25.9, LED25.11, R223.1
unnamed: LED25.5, R222.1
unnamed: LED25.3, R221.1
unnamed: LED25.16, R220.1
unnamed: LED25.14, R219.1
unnamed: LED25.12, LED25.13, R218.1
unnamed: C74.2, JP297.5
unnamed: ATMEGA328P-AU24.20, C75.2
unnamed: LED26.7, R234.1
unnamed: LED26.15, R233.1
unnamed: LED26.9, LED26.11, R232.1
unnamed: LED26.5, R231.1
unnamed: LED26.3, R230.1
unnamed: LED26.16, R229.1
unnamed: LED26.14, R228.1
unnamed: LED26.12, LED26.13, R227.1
unnamed: C77.2, JP309.5
unnamed: ATMEGA328P-AU25.20, C78.2
unnamed: LED27.7, R243.1
unnamed: LED27.15, R242.1
unnamed: LED27.9, LED27.11, R241.1
unnamed: LED27.5, R240.1
unnamed: LED27.3, R239.1
unnamed: LED27.16, R238.1
unnamed: LED27.14, R237.1
unnamed: LED27.12, LED27.13, R236.1
unnamed: C80.2, JP321.5
unnamed: ATMEGA328P-AU26.20, C81.2
unnamed: LED28.7, R252.1
unnamed: LED28.15, R251.1
unnamed: LED28.9, LED28.11, R250.1
unnamed: LED28.5, R249.1
unnamed: LED28.3, R248.1
unnamed: LED28.16, R247.1
unnamed: LED28.14, R246.1
unnamed: LED28.12, LED28.13, R245.1
unnamed: C83.2, JP333.5
unnamed: ATMEGA328P-AU27.20, C84.2
unnamed: LED29.7, R261.1
unnamed: LED29.15, R260.1
unnamed: LED29.9, LED29.11, R259.1
unnamed: LED29.5, R258.1
unnamed: LED29.3, R257.1
unnamed: LED29.16, R256.1
unnamed: LED29.14, R255.1
unnamed: LED29.12, LED29.13, R254.1
unnamed: C86.2, JP345.5
unnamed: ATMEGA328P-AU28.20, C87.2
unnamed: LED30.7, R270.1
unnamed: LED30.15, R269.1
unnamed: LED30.9, LED30.11, R268.1
unnamed: LED30.5, R267.1
unnamed: LED30.3, R266.1
unnamed: LED30.16, R265.1
unnamed: LED30.14, R264.1
unnamed: LED30.12, LED30.13, R263.1
unnamed: C89.2, JP357.5
unnamed: ATMEGA328P-AU29.20, C90.2
RESET: ATMEGA328P-AU.29, C3.1, JP12.7, R1.1
RESET1: ATMEGA328P-AU1.29, C5.1, JP22.7, R5.1
RESET2: ATMEGA328P-AU2.29, C8.1, JP34.7, R19.1
RESET3: ATMEGA328P-AU3.29, C11.1, JP46.7, R28.1
RESET4: ATMEGA328P-AU4.29, C14.1, JP58.7, R37.1
RESET5: ATMEGA328P-AU5.29, C17.1, JP70.7, R46.1
RESET6: ATMEGA328P-AU6.29, C20.1, JP82.7, R55.1
RESET7: ATMEGA328P-AU7.29, C23.1, JP94.7, R64.1
RESET8: ATMEGA328P-AU8.29, C26.1, JP106.7, R73.1
RESET9: ATMEGA328P-AU9.29, C29.1, JP118.7, R82.1
RESET10: ATMEGA328P-AU10.29, C32.1, JP130.7, R91.1
RESET11: ATMEGA328P-AU11.29, C35.1, JP142.7, R100.1
RESET12: ATMEGA328P-AU12.29, C38.1, JP154.7, R109.1
RESET13: ATMEGA328P-AU13.29, C41.1, JP166.7, R118.1
RESET14: ATMEGA328P-AU14.29, C44.1, JP178.7, R127.1
RESET15: ATMEGA328P-AU15.29, C47.1, JP190.7, R136.1
RESET16: ATMEGA328P-AU16.29, C50.1, JP202.7, R145.1
RESET17: ATMEGA328P-AU17.29, C53.1, JP214.7, R154.1
RESET18: ATMEGA328P-AU18.29, C56.1, JP226.7, R163.1
RESET19: ATMEGA328P-AU19.29, C59.1, JP238.7, R172.1
RESET20: ATMEGA328P-AU20.29, C62.1, JP250.7, R181.1
RESET21: ATMEGA328P-AU21.29, C65.1, JP262.7, R190.1
RESET22: ATMEGA328P-AU22.29, C68.1, JP274.7, R199.1
RESET23: ATMEGA328P-AU23.29, C71.1, JP286.7, R208.1
RESET24: ATMEGA328P-AU24.29, C74.1, JP298.7, R217.1
RESET25: ATMEGA328P-AU25.29, C77.1, JP310.7, R226.1
RESET26: ATMEGA328P-AU26.29, C80.1, JP322.7, R235.1
RESET27: ATMEGA328P-AU27.29, C83.1, JP334.7, R244.1
RESET28: ATMEGA328P-AU28.29, C86.1, JP346.7, R253.1
RESET29: ATMEGA328P-AU29.29, C89.1, JP358.7, R262.1
RX: ATMEGA328P-AU.30, JP11.3, JP12.10
RX1: ATMEGA328P-AU1.30, JP21.3, JP22.10
RX2: ATMEGA328P-AU2.30, JP33.3, JP34.10
RX3: ATMEGA328P-AU3.30, JP45.3, JP46.10
RX4: ATMEGA328P-AU4.30, JP57.3, JP58.10
RX5: ATMEGA328P-AU5.30, JP69.3, JP70.10
RX6: ATMEGA328P-AU6.30, JP81.3, JP82.10
RX7: ATMEGA328P-AU7.30, JP93.3, JP94.10
RX8: ATMEGA328P-AU8.30, JP105.3, JP106.10
RX9: ATMEGA328P-AU9.30, JP117.3, JP118.10
RX10: ATMEGA328P-AU10.30, JP129.3, JP130.10
RX11: ATMEGA328P-AU11.30, JP141.3, JP142.10
RX12: ATMEGA328P-AU12.30, JP153.3, JP154.10
RX13: ATMEGA328P-AU13.30, JP165.3, JP166.10
RX14: ATMEGA328P-AU14.30, JP177.3, JP178.10
RX15: ATMEGA328P-AU15.30, JP189.3, JP190.10
RX16: ATMEGA328P-AU16.30, JP201.3, JP202.10
RX17: ATMEGA328P-AU17.30, JP213.3, JP214.10
RX18: ATMEGA328P-AU18.30, JP225.3, JP226.10
RX19: ATMEGA328P-AU19.30, JP237.3, JP238.10
RX20: ATMEGA328P-AU20.30, JP249.3, JP250.10
RX21: ATMEGA328P-AU21.30, JP261.3, JP262.10
RX22: ATMEGA328P-AU22.30, JP273.3, JP274.10
RX23: ATMEGA328P-AU23.30, JP285.3, JP286.10
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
